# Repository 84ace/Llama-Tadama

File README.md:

# Llama-Tadama
BLE Neopixel child's night light

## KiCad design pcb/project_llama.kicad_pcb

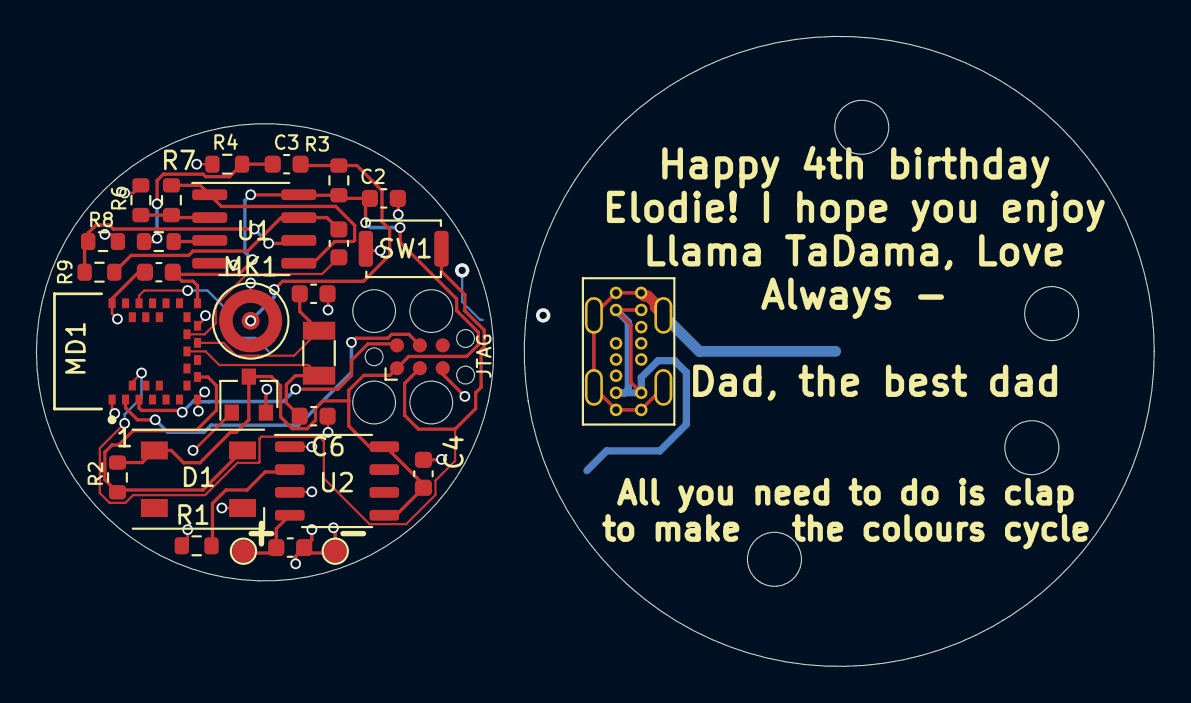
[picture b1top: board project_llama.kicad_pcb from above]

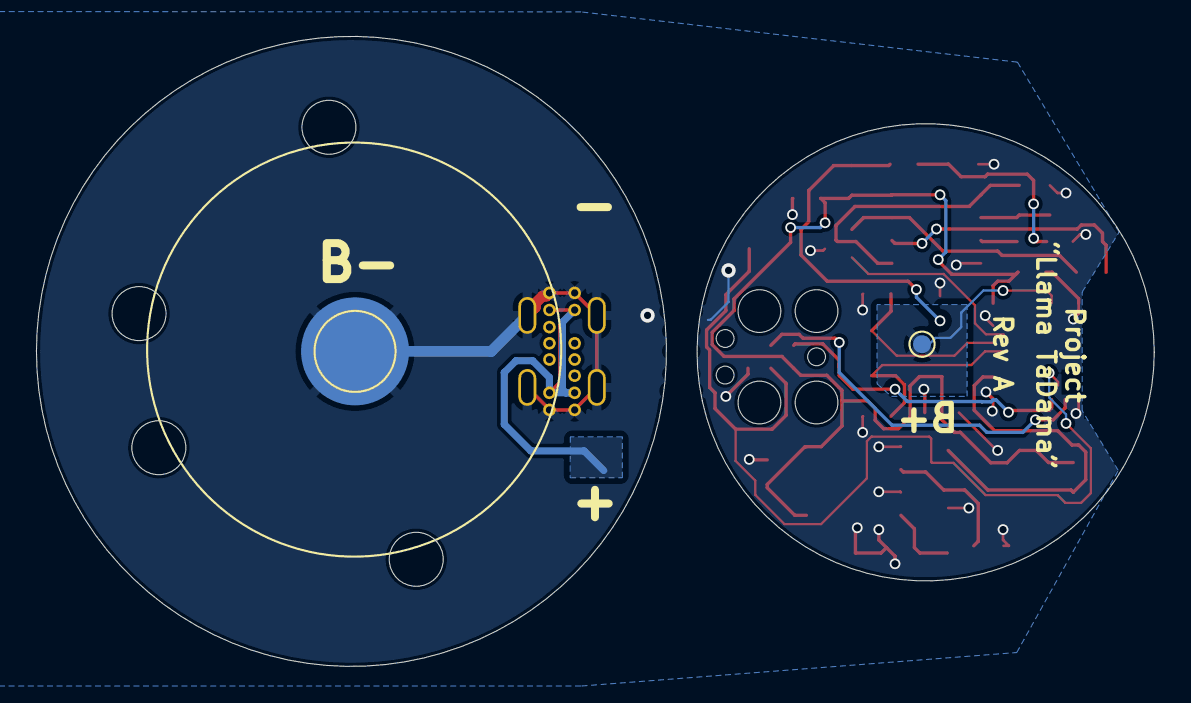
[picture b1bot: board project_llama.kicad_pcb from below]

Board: 2 copper layers, 62.1 x 35.0 mm, 31 parts (2 on the bottom side), 19 nets.

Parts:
C1, C4, C7: 10uF; C_0603_1608Metric
C2: 100n; C_0603_1608Metric
C3: 1uF; C_0603_1608Metric
C5, C6: 12pF; C_0603_1608Metric
C8: 220n; C_0603_1608Metric
D1: WS2812B; LED_WS2812B_PLCC4_5.0x5.0mm_P3.2mm
J1: JTAG_SWD_6; Tag-Connect_TC2030-IDC-FP_2x03_P1.27mm_Vertical
J2: USB_C_Receptacle_USB2.0; USB_C_Receptacle_918-418K2022Y40000_C168704
MD1: MDBT42V-512KV2; Raytac-MDBT42V-512KV2-0-0-MFG
MK1: B4013; CUI_CMC-4013-SMT
Q1: Si2301; SOT-23
R1: 1.2k; R_0603_1608Metric
R2, R3, R7, R9: 10k; R_0603_1608Metric
R4, R5: 100k; R_0603_1608Metric
R6, R8: 1k; R_0603_1608Metric
SW1: TACT-SWITCH; SW_Push_SPST_NO_Alps_SKRK
TP1, TP3: B+; TestPoint_Pad_D1.0mm
TP2: B-; TestPoint_Pad_D4.0mm
TP4: B-; TestPoint_Pad_D1.0mm
U1: LM358; SOIC-8_3.9x4.9mm_P1.27mm
U2: CN3058E_SOP8; SOP-8_3.9x4.9mm_P1.27mm
Y1: Crystal_Small; Crystal_SMD_3215-2Pin_3.2x1.5mm

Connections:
+3V3: C2.2, C4.2, C7.1, D1.1 (VDD), J1.1 (VTref), MD1.20 (VDD), Q1.3 (D), R2.1, R3.2, U1.8 (V+), U2.5 (BAT), U2.8 (FB)
GND: C1.2, C2.1, C4.1, C5.2, C6.1, C7.2, D1.3 (VSS), J1.5 (GND), J2.A1 (GND), J2.A12 (GND), J2.B1 (GND), J2.B12 (GND), J2.S1 (SHIELD), MD1.1 (GND), MD1.10 (GND), MD1.18 (GND), MD1.29 (GND), MK1.1 (-), Q1.1 (G), R1.1, R4.2, R6.2, R8.2, SW1.1, TP2.1, TP4.1, U1.4 (V-), U2.1 (TEMP), U2.3 (GND)
unnamed: C3.1, R4.1, R5.2
unnamed: C3.2, MK1.2 (+), R3.1
unnamed: C5.1, MD1.16 (P0.00/XL1), Y1.1
unnamed: C6.2, MD1.15 (P0.01/XL2), Y1.2
unnamed: C8.2, R9.2, U1.7
unnamed: R1.2, U2.2 (iSET)
unnamed: R5.1, U1.3 (+)
unnamed: R6.1, R7.1, U1.2 (-)
unnamed: R7.2, U1.1, U1.5 (+)
unnamed: R8.1, R9.1, U1.6 (-)
SWCLK: J1.4 (SWDCLK/TCK), MD1.2 (SWDCLK)
SWDIO: J1.2 (SWDIO/TMS), MD1.4 (SWDIO)
VIN: C1.1, J2.A4 (VBUS), J2.A9 (VBUS), J2.B4 (VBUS), J2.B9 (VBUS), TP3.1, U2.4 (VIN)
WS2182B: D1.4 (DIN), MD1.12 (P0.08), R2.2
batt_adc: MD1.26 (P0.02), Q1.2 (S), TP1.1
clap_adc: C8.1, MD1.17 (P0.04)
~Reset: J1.3 (~RESET), MD1.3 (P0.21/RESET), SW1.2

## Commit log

2022-06-06 updates to ino
